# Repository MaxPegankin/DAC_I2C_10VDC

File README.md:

# DAC_I2C_10VDC
I2C to MCP4725 to 0 . . 10VDC (from 24VDC) 

## Description
Digital Analog Converter</br>
Breakout board to convert I2C signal to 0 .. 10 VDC</br>
Designed with **Kicad 8** </br>
Mainly based on **MCP4725** </br>
3.3v or 5v power supply acceptable for I2C interface</br>
24VDC used for 0 .. 10VDC generation.</br>

Can be used with Arduino and Raspberry Pi boards.

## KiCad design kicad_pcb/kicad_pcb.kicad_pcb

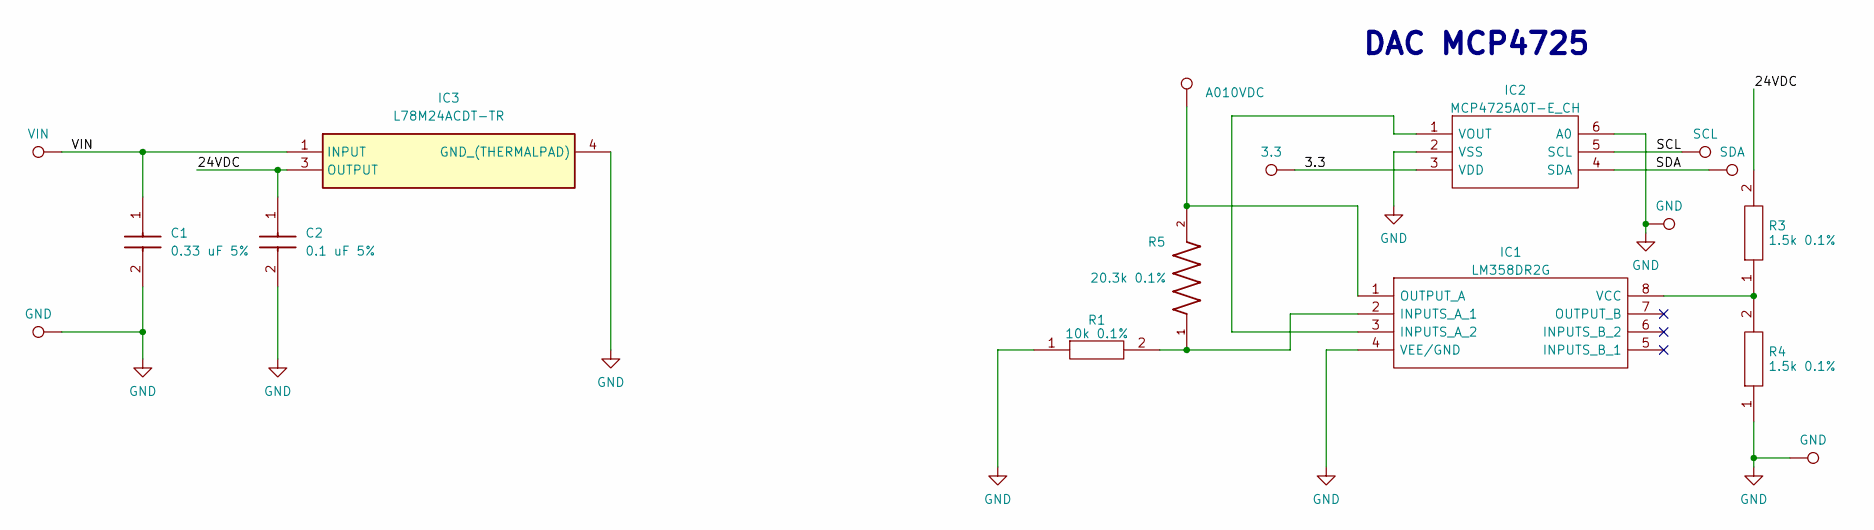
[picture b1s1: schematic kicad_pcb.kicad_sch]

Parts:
C1: 0.33 uF 5%; C0805; Mouser Part Number 80-C0805C334J5RAUTO
C2: 0.1 uF 5%; C0805; Mouser Part Number 80-C0805R104J5RACTU
IC1: LM358DR2G; SOIC127P600X175-8N; Mouser Part Number 863-LM358DR2G
IC2: MCP4725A0T-E_CH; SOT95P270X145-6N; Mouser Part Number 579-MCP4725A0TECH
IC3: L78M24ACDT-TR; TO228P972X240-3N; Mouser Part Number 511-L78M24ACDT-TR
R1: 10k 0.1%; RESC2012X55N; Mouser Part Number 71-TNPW080510K0BEEA
R3, R4: 1.5k 0.1%; RESC2012X55N; Mouser Part Number 71-TNPW08051K50BEEA
R5: 20.3k 0.1%; RN73H1JTTD2032B25_RESC1608X55N
TP1: VIN; TestPoint_THTPad_D2.0mm_Drill1.0mm
TP2: 3.3; TestPoint_THTPad_D2.0mm_Drill1.0mm
TP3: SCL; TestPoint_THTPad_D2.0mm_Drill1.0mm
TP4: SDA; TestPoint_THTPad_D2.0mm_Drill1.0mm
TP5, TP7, TP8: GND; TestPoint_THTPad_D2.0mm_Drill1.0mm
TP6: A010VDC; TestPoint_THTPad_D2.0mm_Drill1.0mm

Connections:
/3.3: IC2.3 (VDD), TP2.1
/24VDC: C2.1, IC3.3 (OUTPUT), R3.2
/SCL: IC2.5 (SCL), TP3.1
/SDA: IC2.4 (SDA), TP4.1
/VIN: C1.1, IC3.1 (INPUT), TP1.1
GND: C1.2, C2.2, IC1.4 (VEE/GND), IC2.2 (VSS), IC2.6 (A0), IC3.4 (GND_(THERMALPAD)), R1.1, R4.1, TP5.1, TP7.1, TP8.1
unnamed: IC1.2 (INPUTS_A_1), R1.2, R5.1
unnamed: IC1.3 (INPUTS_A_2), IC2.1 (VOUT)
unnamed: IC1.1 (OUTPUT_A), R5.2, TP6.1
unnamed: IC1.8 (VCC), R3.1, R4.2

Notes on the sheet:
DAC MCP4725

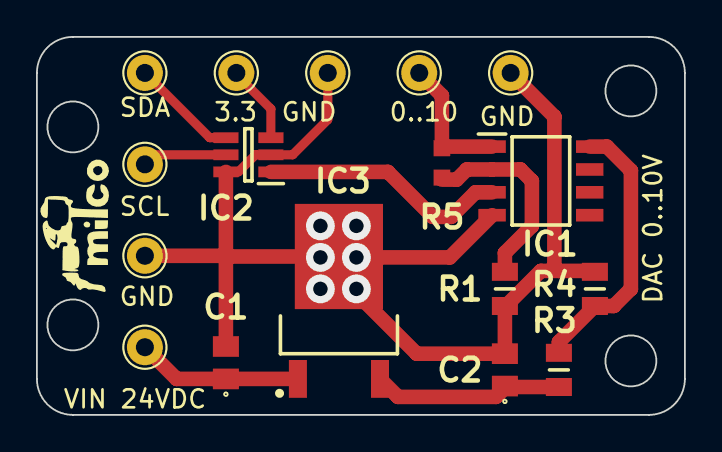
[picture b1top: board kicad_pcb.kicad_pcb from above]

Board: 2 copper layers, 36.0 x 21.0 mm, 17 parts (0 on the bottom side), 10 nets.

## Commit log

2024-04-29 20.3k rsistor update
2024-04-29 photo update
2024-04-29 20.3k resistor update to KOA
